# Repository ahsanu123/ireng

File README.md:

<p>

</p>

<p align="center">
   <br/>
</p>

# ✒️ Introduction 

Ireng is custom Black Magic Probe Based on STM32F103RCT. Only for fun 😙 and learning about debugging in microcontroller.

<details>
  <summary>expands me!!</summary>
     <br/>
</details>

## 🌳 TODO LOG

- ~~Add SPI Flash from windbond, jumat 17 januari 2025 at 19:51~~, no pin left for spi and dont want to change pinout of original schematic.
- ~~re-check schematic,  jumat 17 januari 2025 at 19:51~~
- add usb type c, and use usb micro b as backup,  jumat 17 januari 2025 at 19:51

## 🧱 Reference 

- [Black Magic Probe Book](https://www.compuphase.com/electronics/BlackMagicProbe.pdf)
- [STM32F10xxx Getting Started Hardware Development](https://www.st.com/resource/en/application_note/an2586-getting-started-with-stm32f10xxx-hardware-development-stmicroelectronics.pdf)

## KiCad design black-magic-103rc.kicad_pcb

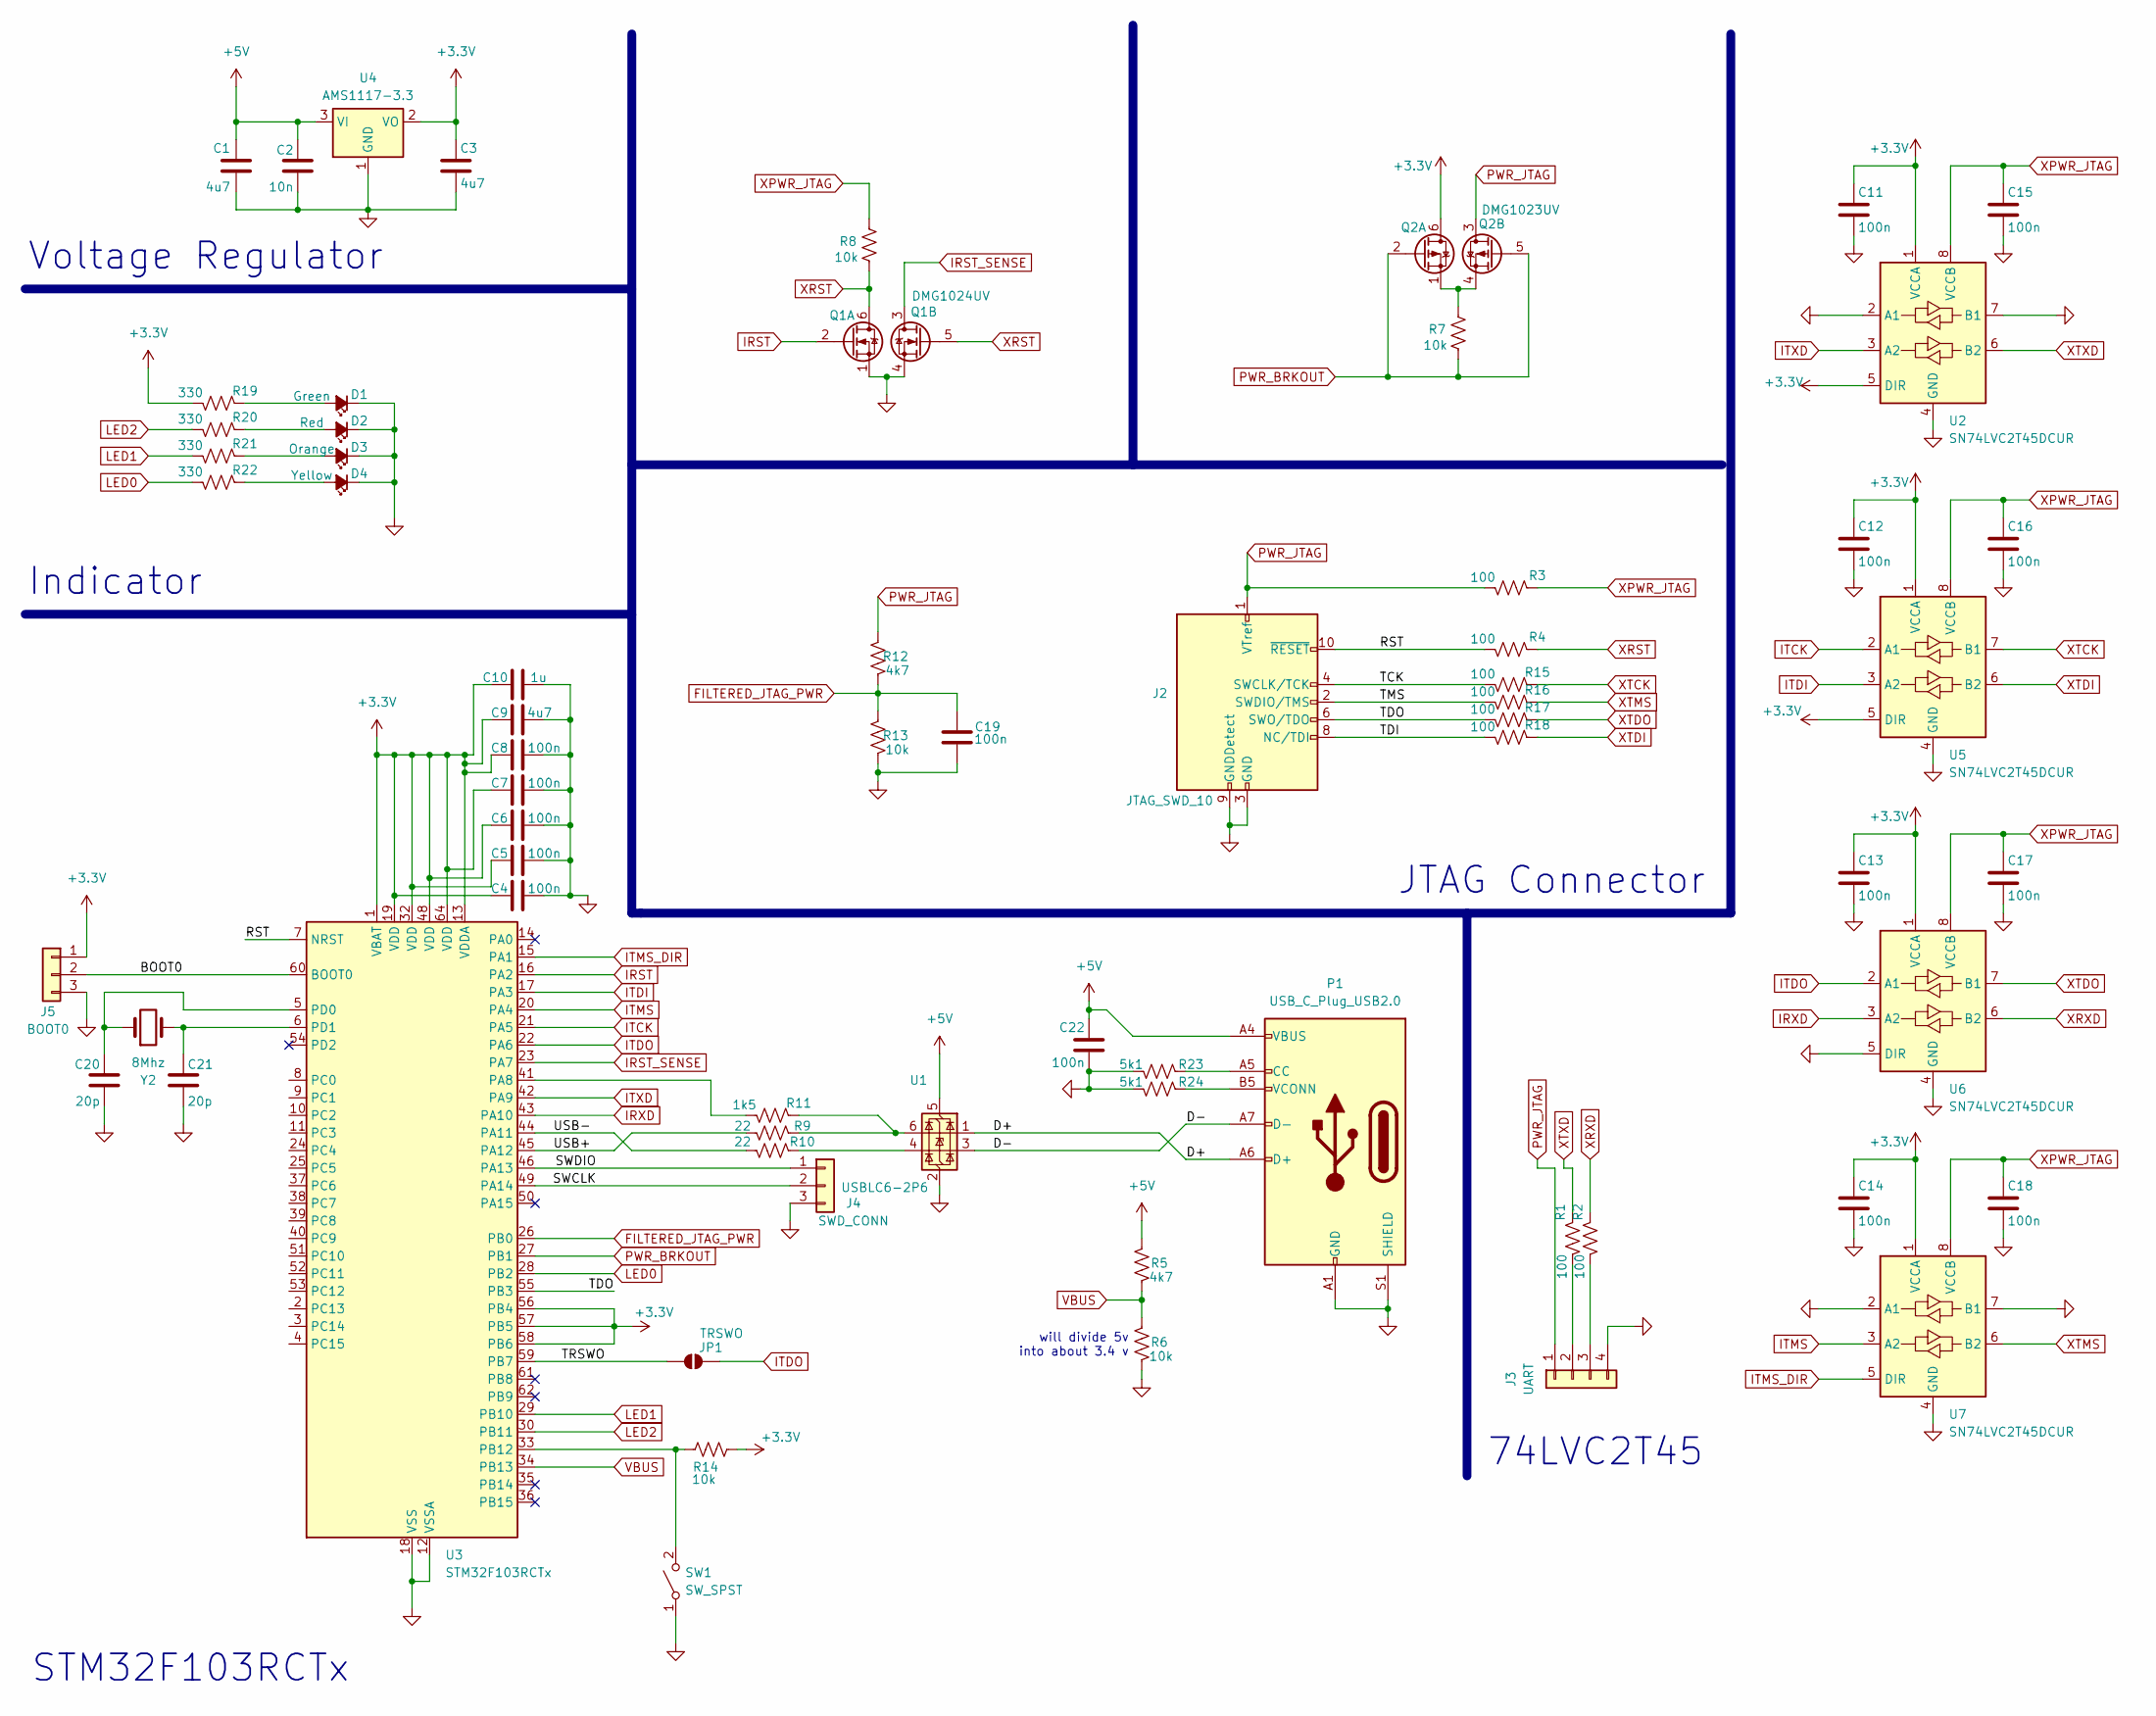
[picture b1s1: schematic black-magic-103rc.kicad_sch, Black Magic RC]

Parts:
C1, C3, C9: 4u7; C_0603_1608Metric_Pad1.08x0.95mm_HandSolder
C2: 10n; C_0603_1608Metric_Pad1.08x0.95mm_HandSolder
C4, C5, C6, C7, C8, C11, C12, C13, C14, C15, C16, C17, C18, C19, C22: 100n; C_0603_1608Metric_Pad1.08x0.95mm_HandSolder
C10: 1u; C_0603_1608Metric_Pad1.08x0.95mm_HandSolder
C20, C21: 20p; C_0603_1608Metric_Pad1.08x0.95mm_HandSolder
D1: Green; LED_0805_2012Metric_Pad1.15x1.40mm_HandSolder
D2: Red; LED_0805_2012Metric_Pad1.15x1.40mm_HandSolder
D3: Orange; LED_0805_2012Metric_Pad1.15x1.40mm_HandSolder
D4: Yellow; LED_0805_2012Metric_Pad1.15x1.40mm_HandSolder
J2: JTAG_SWD_10; PinHeader_2x05_P2.54mm_Horizontal
J3: UART; PinHeader_1x04_P2.54mm_Vertical
J4: SWD_CONN; PinHeader_1x03_P2.54mm_Vertical
J5: BOOT0; PinHeader_1x03_P2.54mm_Vertical
JP1: TRSWO; SolderJumper-2_P1.3mm_Open_RoundedPad1.0x1.5mm
P1: USB_C_Plug_USB2.0; USB_C_Receptacle_GCT_USB4110
Q1: DMG1024UV; SOT-563
Q2: DMG1023UV; SOT-563
R1, R2, R3, R4, R15, R16, R17, R18: 100; R_0805_2012Metric_Pad1.20x1.40mm_HandSolder
R5, R12: 4k7; R_0805_2012Metric_Pad1.20x1.40mm_HandSolder
R6, R7, R8, R13, R14: 10k; R_0805_2012Metric_Pad1.20x1.40mm_HandSolder
R9, R10: 22; R_0805_2012Metric_Pad1.20x1.40mm_HandSolder
R11: 1k5; R_0805_2012Metric_Pad1.20x1.40mm_HandSolder
R19, R20, R21, R22: 330; R_0805_2012Metric_Pad1.20x1.40mm_HandSolder
R23, R24: 5k1; R_0805_2012Metric_Pad1.20x1.40mm_HandSolder
SW1: SW_SPST; SW_Push_1P1T_NO_6x6mm_H9.5mm
U1: USBLC6-2P6; SOT-666
U2, U5, U6, U7: SN74LVC2T45DCUR; VSSOP-8_2.4x2.1mm_P0.5mm
U3: STM32F103RCTx; LQFP-64_10x10mm_P0.5mm
U4: AMS1117-3.3; SOT-223-3_TabPin2
Y2: 8Mhz; Crystal_HC18-U_Vertical

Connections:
+3.3V: C3.1, C4.1, C5.1, C6.1, C7.1, C8.1, C9.1, C10.1, C11.1, C12.1, C13.1, C14.1, J5.1, Q2.6 (D), R14.1, R19.2, U2.1 (VCCA), U2.5 (DIR), U3.1 (VBAT), U3.13 (VDDA), U3.19 (VDD), U3.32 (VDD), U3.48 (VDD), U3.56 (PB4), U3.57 (PB5), U3.58 (PB6), U3.64 (VDD), U4.2 (VO), U5.1 (VCCA), U5.5 (DIR), U6.1 (VCCA), U7.1 (VCCA)
+5V: C1.1, C2.1, C22.1, P1.A4 (VBUS), P1.A9 (VBUS), P1.B4 (VBUS), P1.B9 (VBUS), R5.2, U1.5 (VBUS), U4.3 (VI)
/BOOT0: J5.2, U3.60 (BOOT0)
/D+: P1.A6 (D+), U1.1 (I/O1)
/D-: P1.A7 (D-), U1.3 (I/O2)
/RST: J2.10 (~RESET), R4.2, U3.7 (NRST)
/SWCLK: J4.2, U3.49 (PA14)
/SWDIO: J4.1, U3.46 (PA13)
/TCK: J2.4 (SWCLK/TCK), R15.2
/TDI: J2.8 (NC/TDI), R18.2
/TDO: J2.6 (SWO/TDO), R17.2, U3.55 (PB3)
/TMS: J2.2 (SWDIO/TMS), R16.2
/TRSWO: JP1.1 (A), U3.59 (PB7)
/USB+: R9.2, U3.45 (PA12)
/USB-: R10.2, U3.44 (PA11)
FILTERED_JTAG_PWR: C19.1, R12.1, R13.2, U3.26 (PB0)
GND: C1.2, C2.2, C3.2, C4.2, C5.2, C6.2, C7.2, C8.2, C9.2, C10.2, C11.2, C12.2, C13.2, C14.2, C15.2, C16.2, C17.2, C18.2, C19.2, C20.2, C21.2, C22.2, D1.1 (K), D2.1 (K), D3.1 (K), D4.1 (K), J2.3 (GND), J2.5 (GND), J2.9 (GNDDetect), J3.4, J4.3, J5.3, P1.A1 (GND), P1.A12 (GND), P1.B1 (GND), P1.B12 (GND), P1.S1 (SHIELD), Q1.1 (S), Q1.4 (S), R6.1, R13.1, R23.1, R24.1, SW1.1 (A), U1.2 (GND), U2.2 (A1), U2.4 (GND), U2.7 (B1), U3.12 (VSSA), U3.18 (VSS), U3.31 (VSS), U3.47 (VSS), U3.63 (VSS), U4.1 (GND), U5.4 (GND), U6.4 (GND), U6.5 (DIR), U7.2 (A1), U7.4 (GND), U7.7 (B1)
IRST: Q1.2 (G), U3.16 (PA2)
IRST_SENSE: Q1.3 (D), U3.23 (PA7)
IRXD: U3.43 (PA10), U6.3 (A2)
ITCK: U3.21 (PA5), U5.2 (A1)
ITDI: U3.17 (PA3), U5.3 (A2)
ITDO: JP1.2 (B), U3.22 (PA6), U6.2 (A1)
ITMS: U3.20 (PA4), U7.3 (A2)
ITMS_DIR: U3.15 (PA1), U7.5 (DIR)
ITXD: U2.3 (A2), U3.42 (PA9)
LED0: R22.2, U3.28 (PB2)
LED1: R21.2, U3.29 (PB10)
LED2: R20.2, U3.30 (PB11)
unnamed: D1.2 (A), R19.1
unnamed: D2.2 (A), R20.1
unnamed: D3.2 (A), R21.1
unnamed: D4.2 (A), R22.1
unnamed: J3.2, R1.2
unnamed: J3.3, R2.2
unnamed: P1.A5 (CC), R23.2
unnamed: P1.B5 (VCONN), R24.2
unnamed: Q2.1 (S), Q2.4 (S), R7.2
unnamed: R10.1, U1.4 (I/O2)
unnamed: R9.1, R11.1, U1.6 (I/O1)
unnamed: R14.2, SW1.2 (B), U3.33 (PB12)
unnamed: R11.2, U3.41 (PA8)
unnamed: C20.1, U3.5 (PD0), Y2.1
unnamed: C21.1, U3.6 (PD1), Y2.2
PWR_BRKOUT: Q2.2 (G), Q2.5 (G), R7.1, U3.27 (PB1)
PWR_JTAG: J2.1 (VTref), J3.1, Q2.3 (D), R3.2, R12.2
VBUS: R5.1, R6.2, U3.34 (PB13)
XPWR_JTAG: C15.1, C16.1, C17.1, C18.1, R3.1, R8.2, U2.8 (VCCB), U5.8 (VCCB), U6.8 (VCCB), U7.8 (VCCB)
XRST: Q1.5 (G), Q1.6 (D), R4.1, R8.1
XRXD: R2.1, U6.6 (B2)
XTCK: R15.1, U5.7 (B1)
XTDI: R18.1, U5.6 (B2)
XTDO: R17.1, U6.7 (B1)
XTMS: R16.1, U7.6 (B2)
XTXD: R1.1, U2.6 (B2)

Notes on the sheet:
74LVC2T45
JTAG Connector
Voltage Regulator
Indicator
STM32F103RCTx
will divide 5v into about 3.4 v

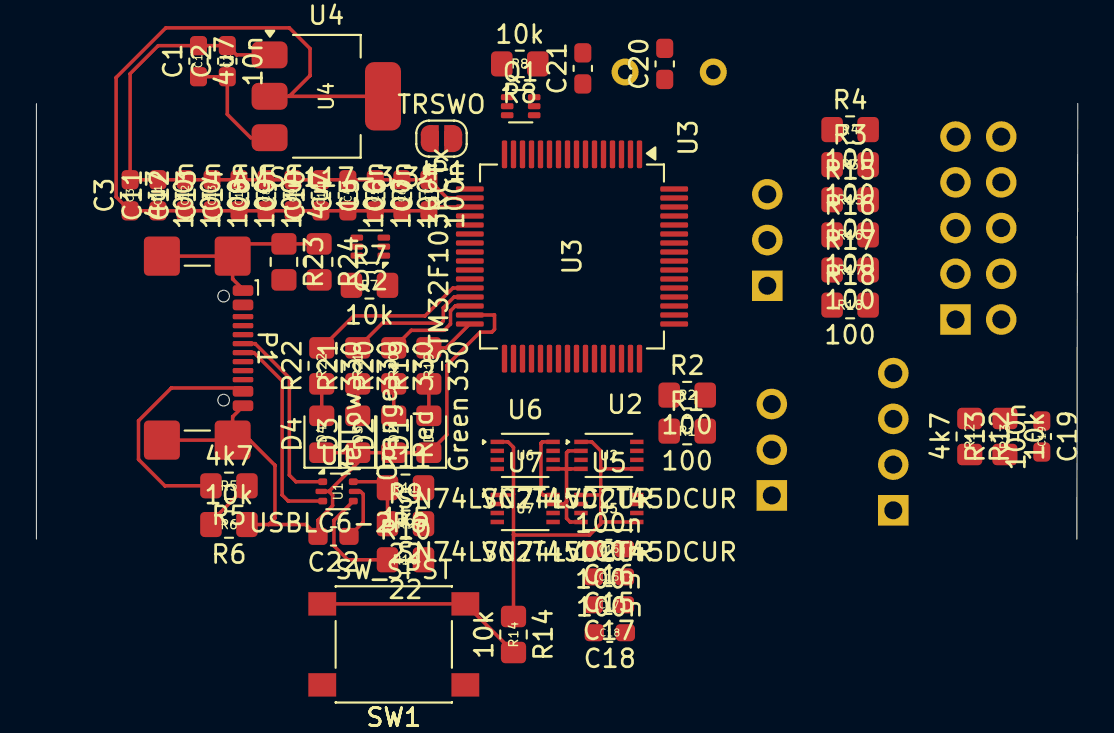
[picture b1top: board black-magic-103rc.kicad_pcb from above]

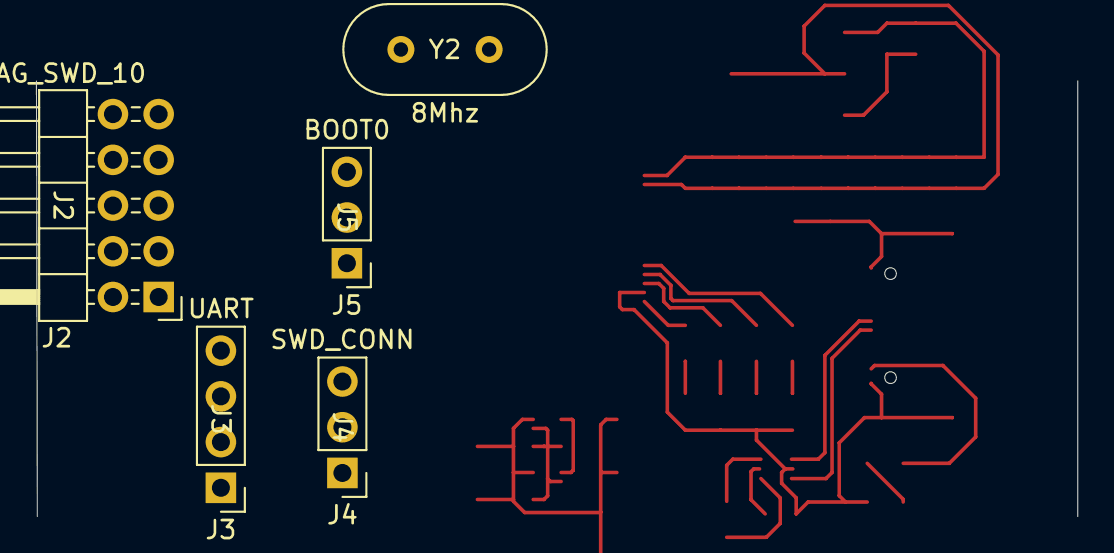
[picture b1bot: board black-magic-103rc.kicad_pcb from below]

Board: 2 copper layers, 57.9 x 24.2 mm, 67 parts (5 on the bottom side), 55 nets.

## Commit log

2025-01-17 [01-17-1811] moved black magic probe to new ireng repository
2025-01-17 [01-17-1825] adding simple description and logo
    Update README.md
2025-01-17 [01-17-1939] copied schematic from reference, need to re-confirm
    Update README.md
2025-01-19 [01-19-2111] finish basic board component placement
    nit
2025-02-04 [02-04-1948] start to routing
2025-05-25 [05-25-1348] generate bom
2025-06-05 [06-05-1334] update after stagnate
